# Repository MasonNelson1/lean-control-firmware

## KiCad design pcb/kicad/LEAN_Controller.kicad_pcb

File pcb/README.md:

# LEAN PCBs (Mason's KiCad project, Rev M, 2026-10-19)

Trimmed from the Drive zip on 2026-11-21: backups, gerbers, 3D exports and
fabrication zips removed. The full original is still on the team Drive.

- `kicad/` schematic (5 sheets), board, project, symbol + footprint libraries. Plain text: grep nets.
- `docs/` Mason's design notes (wiring, Bluetooth, power switch, rotary switches, panel).
- `csv/` connector pinouts, BOM, Teensy pin map (`old_number` = footprint pad, NOT Teensy pin).
- `previews/` schematic and assembly PNGs.
- `datasheets/` assembly guide, control-board V2/V3 drawings, Pololu regulator, rotary switch, VESC (TRAMPA MkVI) manual.
- `vesc-reference/` VESC hw config source and appconf parameter definitions.

## Teensy pin → net (read from the board copper, matches firmware `src/common.h`)
| Pin | Net | Pin | Net |
|---|---|---|---|
| 0 / 1 | Bluetooth TX→RX / RX←TX (Serial1, J22) | 24 / 25 / 26 | BTN LEAN / DISARM / REMOTE |
| 2 / 32 | BT EN / STATE (R65/R66 DNP, disconnected) | 27–31 | LED CAL / LEAN / DISARM / REMOTE / CONNECTED |
| 4 | Calibrate button (J5.2) | A0 / A1 | SPEED / ACCEL knob |
| 22 / 23 | CAN1 TX / RX → MCP2562 | A14–A17 | FSR4 J9 / FSR3 J8 / FSR2 J7 / FSR1 J6 |

Firmware sensor roles: J6/A17 back, J7/A16 right, J8/A15 front, J9/A14 left.
VESC: J2 primary = 5 V, GND, CANH, CANL. J1 secondary = CAN only.

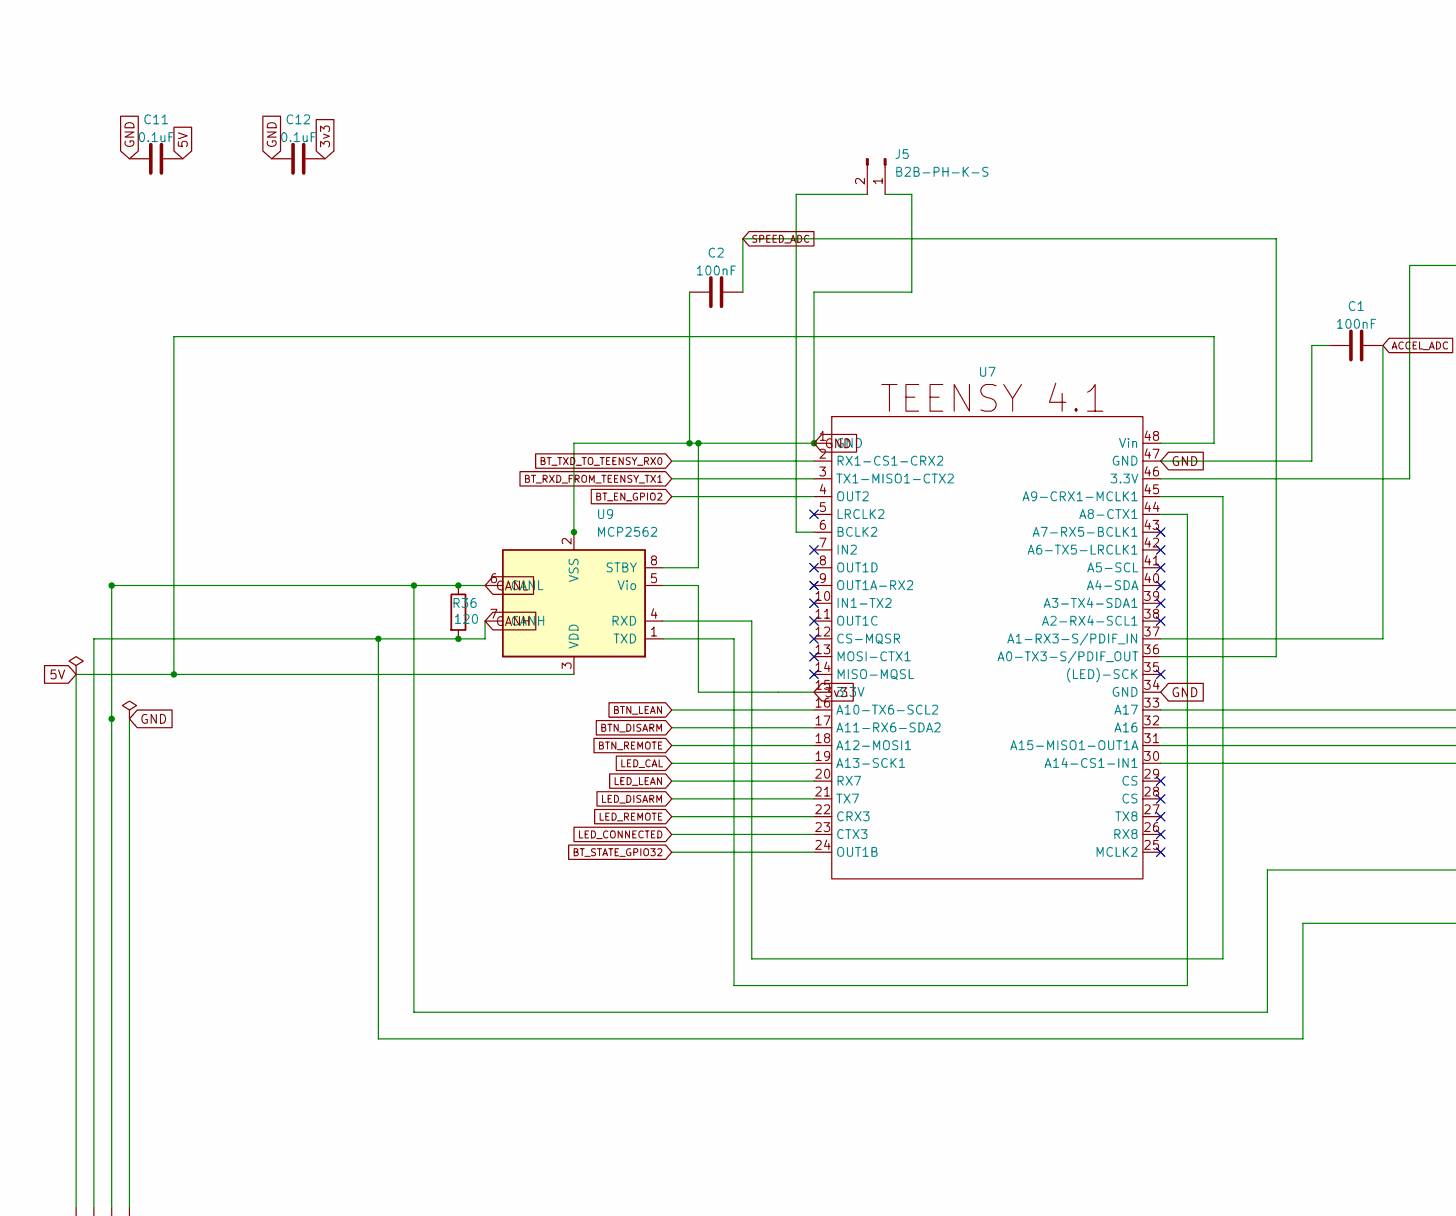
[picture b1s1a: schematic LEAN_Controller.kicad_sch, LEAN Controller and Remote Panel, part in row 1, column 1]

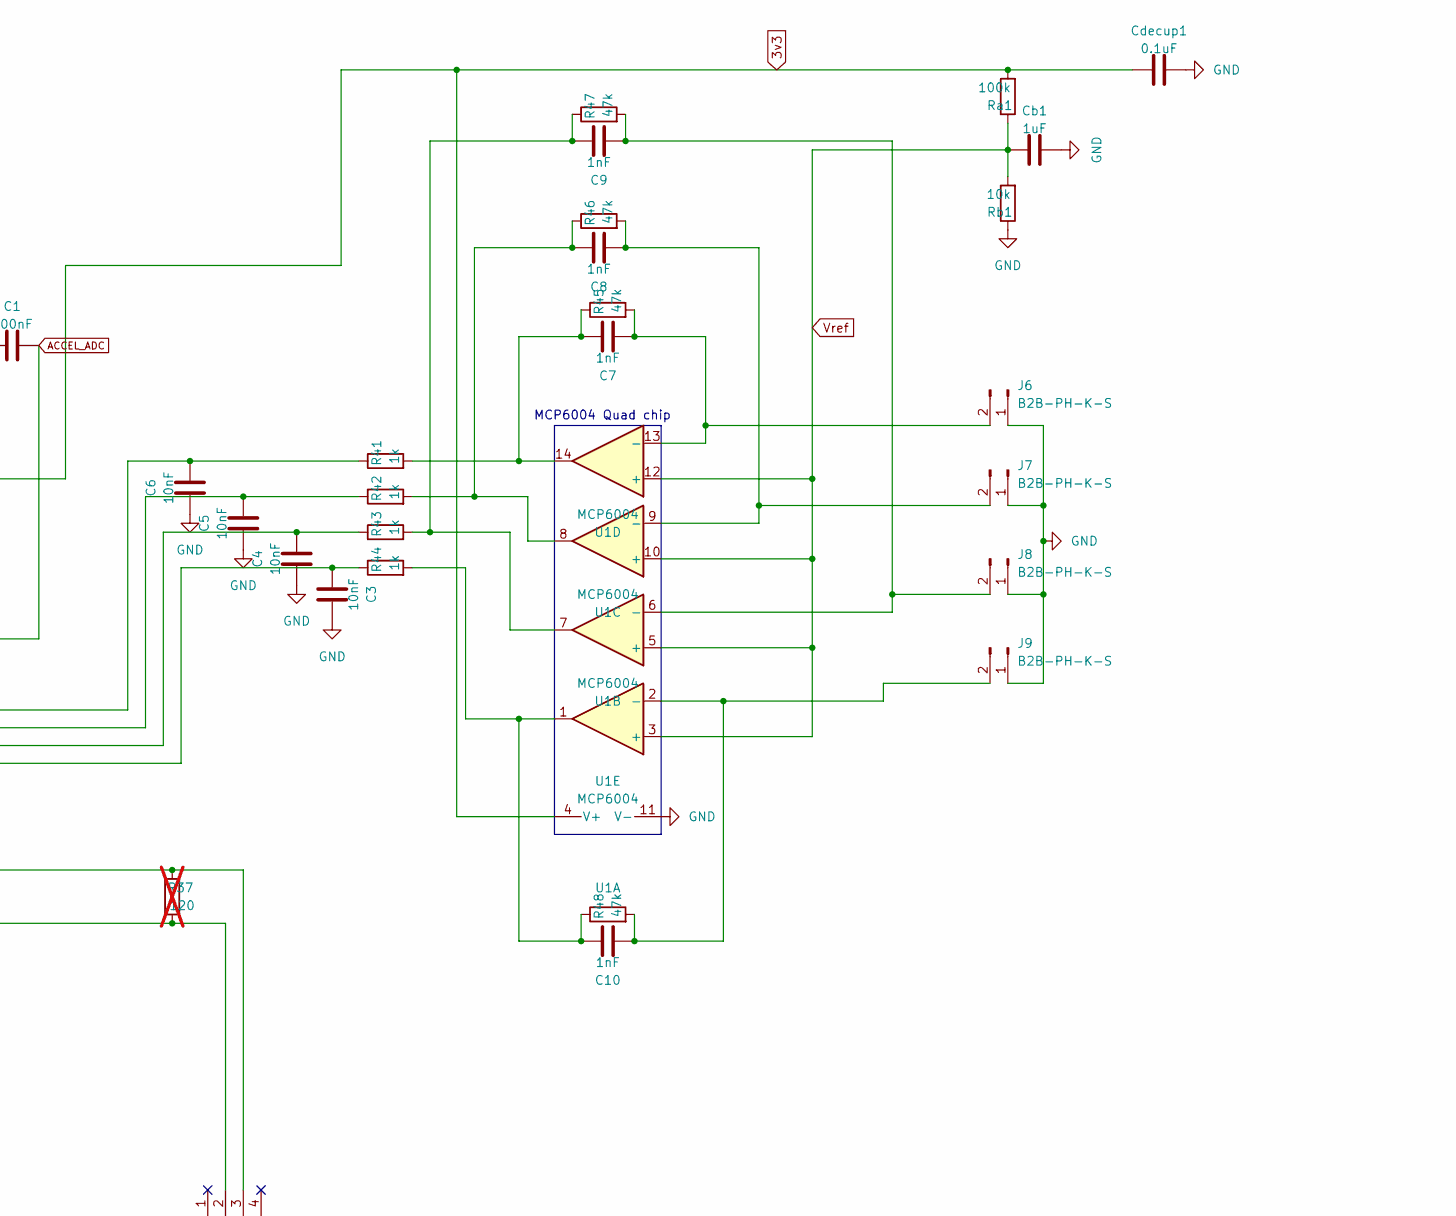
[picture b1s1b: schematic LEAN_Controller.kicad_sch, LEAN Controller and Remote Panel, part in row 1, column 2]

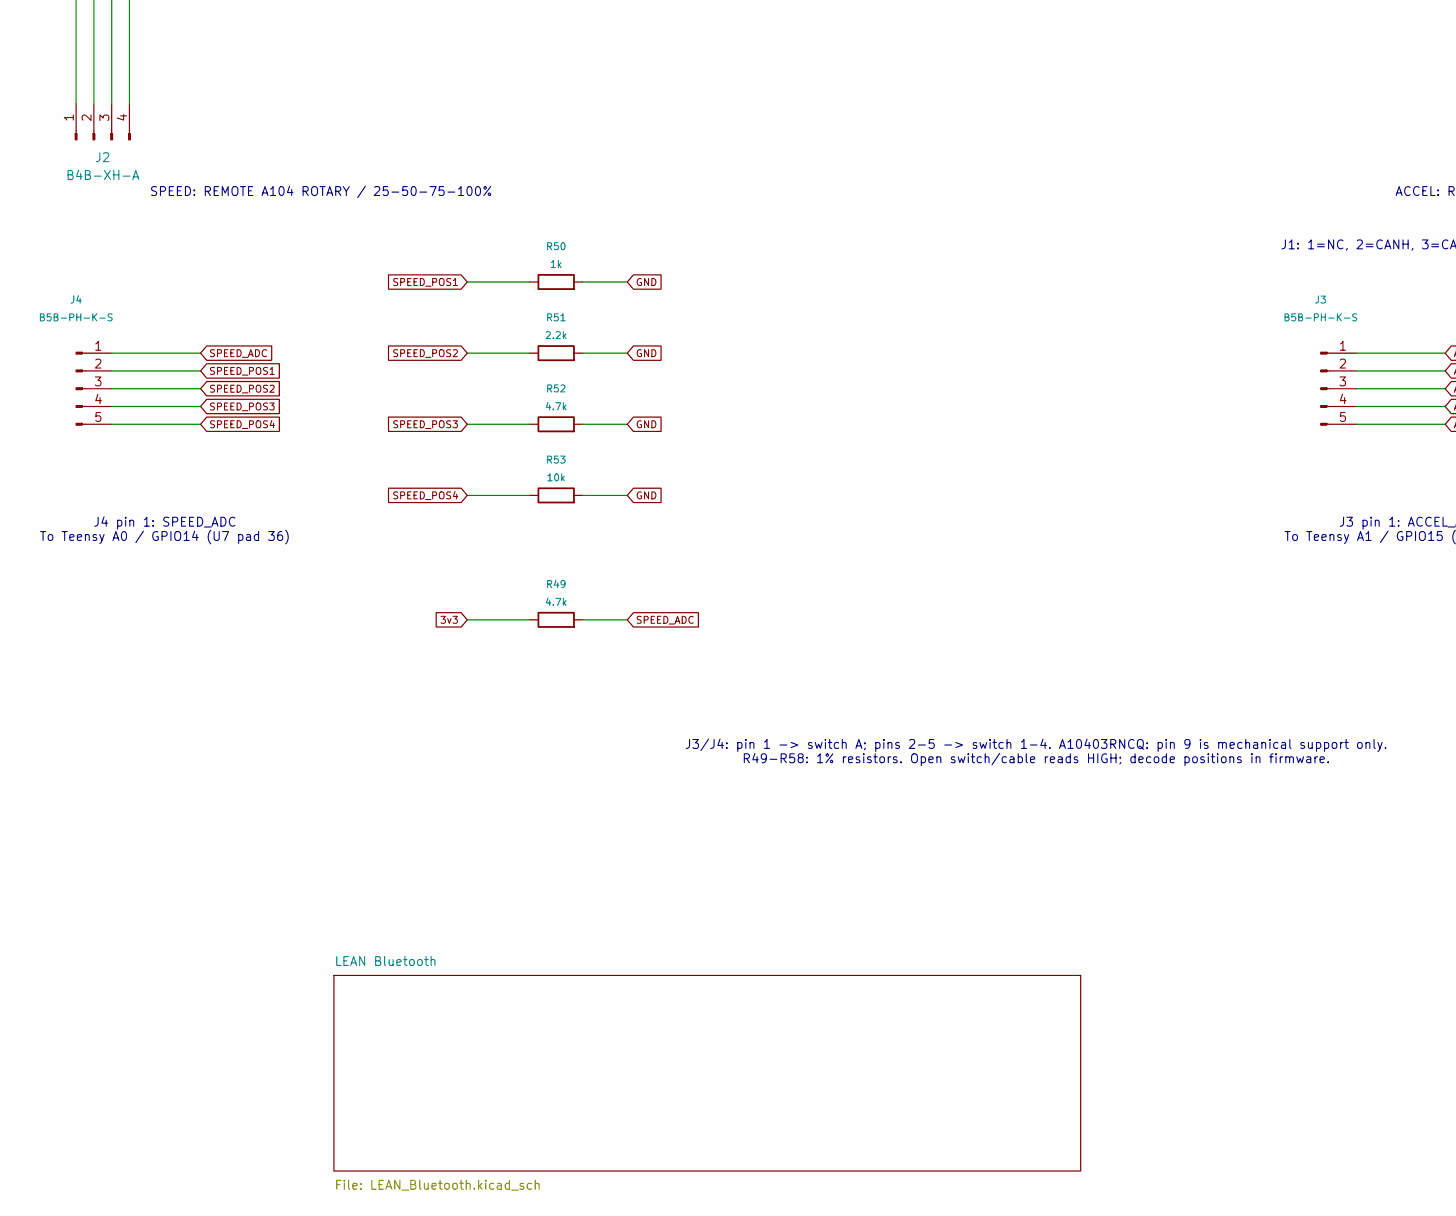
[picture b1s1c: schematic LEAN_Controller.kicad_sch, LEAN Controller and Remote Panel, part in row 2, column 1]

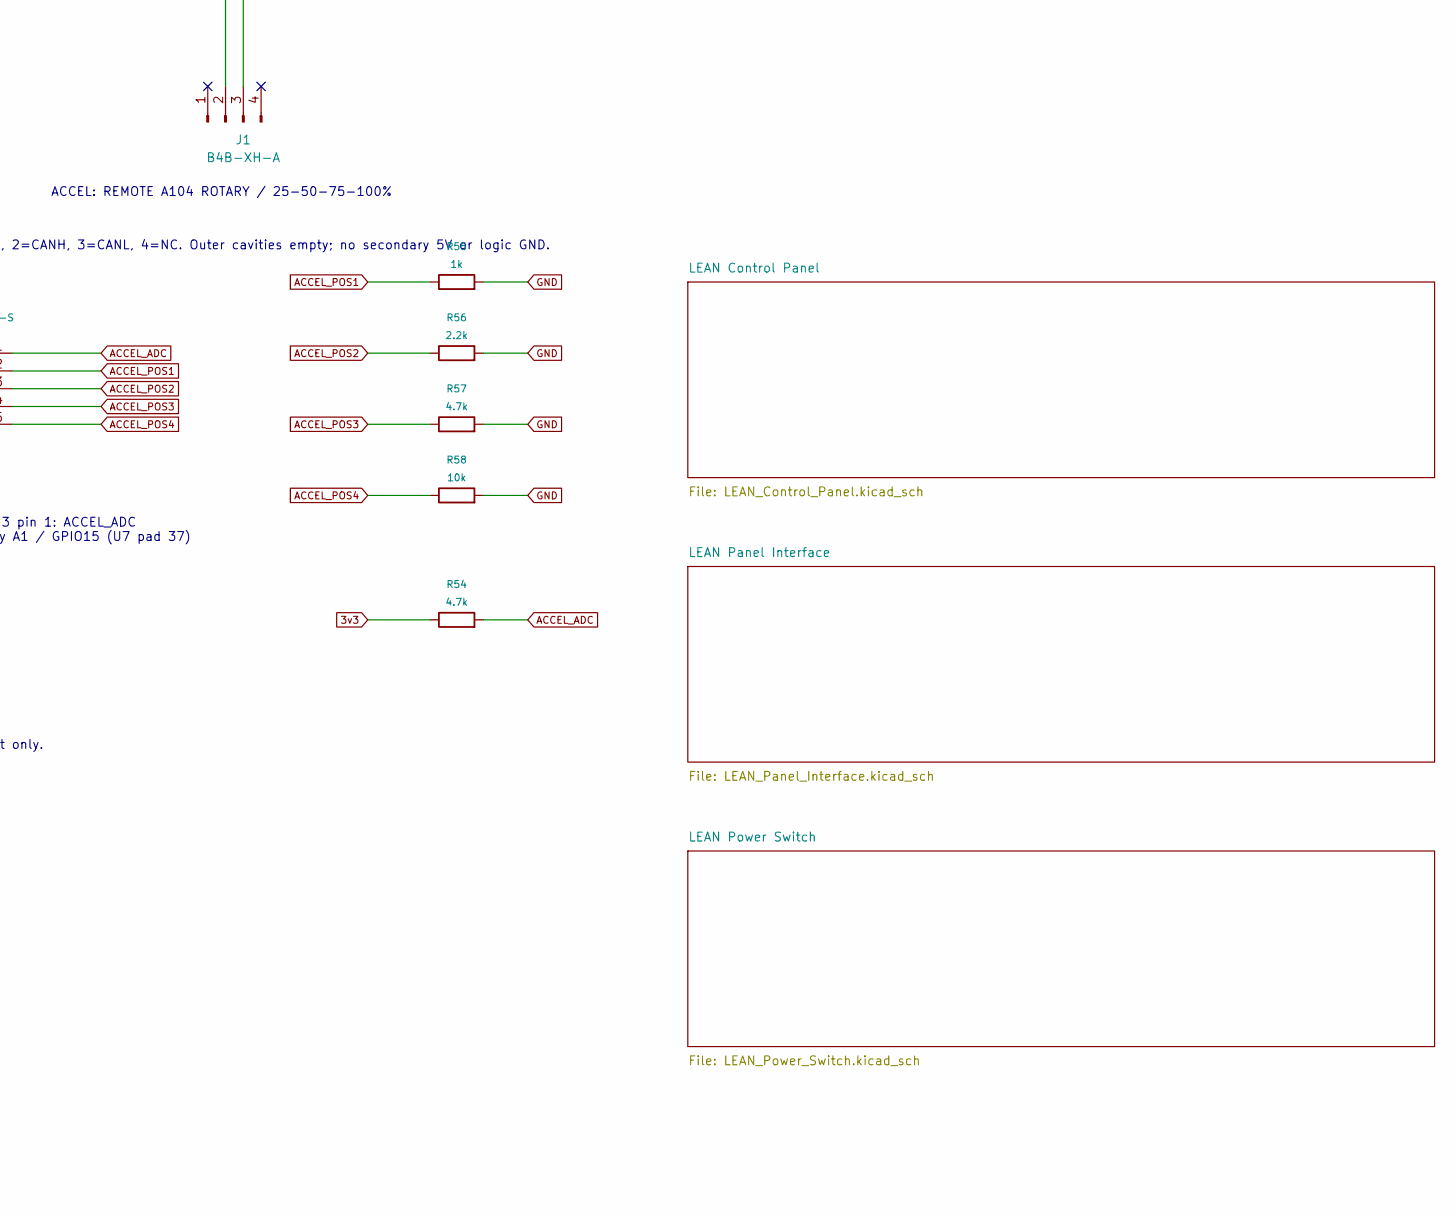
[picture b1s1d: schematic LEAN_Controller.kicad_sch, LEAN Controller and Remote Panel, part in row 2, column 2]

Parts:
C1, C2: 100nF; C_Disc_D5.0mm_W2.5mm_P5.00mm
C3, C4, C5, C6: 10nF; C_Disc_D5.0mm_W2.5mm_P5.00mm
C7, C8, C9, C10: 1nF; C_Disc_D5.0mm_W2.5mm_P5.00mm
C11, C12: 0.1uF; C_Disc_D5.0mm_W2.5mm_P5.00mm
Cb1: 1uF; C_Disc_D5.0mm_W2.5mm_P5.00mm
Cdecup1: 0.1uF; C_Disc_D5.0mm_W2.5mm_P5.00mm
J1, J2: B4B-XH-A; JST_XH_B4B-XH-A_1x04_P2.50mm_Vertical
J3, J4: B5B-PH-K-S; JST_PH_B5B-PH-K_1x05_P2.00mm_Vertical
J5, J6, J7, J8, J9: B2B-PH-K-S; JST_PH_B2B-PH-K_1x02_P2.00mm_Vertical
R36: 120; R_Axial_DIN0207_L6.3mm_D2.5mm_P7.62mm_Horizontal
R37: 120; R_Axial_DIN0207_L6.3mm_D2.5mm_P7.62mm_Horizontal; not fitted
R41, R42, R43, R44, R50, R55: 1k; R_Axial_DIN0207_L6.3mm_D2.5mm_P7.62mm_Horizontal
R45, R46, R47, R48: 47k; R_Axial_DIN0207_L6.3mm_D2.5mm_P7.62mm_Horizontal
R49, R52, R54, R57: 4.7k; R_Axial_DIN0207_L6.3mm_D2.5mm_P7.62mm_Horizontal
R51, R56: 2.2k; R_Axial_DIN0207_L6.3mm_D2.5mm_P7.62mm_Horizontal
R53, R58: 10k; R_Axial_DIN0207_L6.3mm_D2.5mm_P7.62mm_Horizontal
Ra1: 100k; R_Axial_DIN0207_L6.3mm_D2.5mm_P7.62mm_Horizontal
Rb1: 10k; R_Axial_DIN0207_L6.3mm_D2.5mm_P7.62mm_Horizontal
U1: MCP6004; DIP-14_W7.62mm
U7: Teensy41
U9: MCP2562; DIP-8_W7.62mm

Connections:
3v3: C12.2, Cdecup1.1, R49.1, R54.1, Ra1.2, U1.4 (V+), U7.15 (A1-RX3-S/PDIF_IN), U7.46 (3.3V), U9.5 (Vio); also elsewhere on the board
5V: C11.2, J2.1, U7.48 (Vin), U9.3 (VDD); also elsewhere on the board
ACCEL_ADC: C1.2, J3.1, R54.2, U7.37 (CS)
ACCEL_POS1: J3.2, R55.1
ACCEL_POS2: J3.3, R56.1
ACCEL_POS3: J3.4, R57.1
ACCEL_POS4: J3.5, R58.1
BTN_DISARM: U7.17 (A3-TX4-SDA1); also elsewhere on the board
BTN_LEAN: U7.16 (A2-RX4-SCL1); also elsewhere on the board
BTN_REMOTE: U7.18 (A4-SDA); also elsewhere on the board
BT_EN_GPIO2: U7.4 (BCLK2); also elsewhere on the board
BT_RXD_FROM_TEENSY_TX1: U7.3 (LRCLK2); also elsewhere on the board
BT_STATE_GPIO32: U7.24 (A10-TX6-SCL2); also elsewhere on the board
BT_TXD_TO_TEENSY_RX0: U7.2 (OUT2); also elsewhere on the board
CANH: J1.2, J2.2, R36.2, R37.2, U9.7 (CANH)
CANL: J1.3, J2.3, R36.1, R37.1, U9.6 (CANL)
GND: C1.1, C2.1, C3.2, C4.1, C5.1, C6.1, C11.1, C12.1, Cb1.2, Cdecup1.2, J2.4, J5.1, J6.1, J7.1, J8.1, J9.1, R50.2, R51.2, R52.2, R53.2, R55.2, R56.2, R57.2, R58.2, Rb1.1, U1.11 (V-), U7.1 (TX1-MISO1-CTX2), U7.34 (RX8), U7.47 (GND), U9.2 (VSS), U9.8 (STBY); also elsewhere on the board
LED_CAL: U7.19 (A5-SCL); also elsewhere on the board
LED_CONNECTED: U7.23 (A9-CRX1-MCLK1); also elsewhere on the board
LED_DISARM: U7.21 (A7-RX5-BCLK1); also elsewhere on the board
LED_LEAN: U7.20 (A6-TX5-LRCLK1); also elsewhere on the board
LED_REMOTE: U7.22 (A8-CTX1); also elsewhere on the board
unnamed: C7.2, R41.2, R45.1, U1.14
unnamed: C8.2, R42.2, R46.1, U1.8
unnamed: C9.2, R43.2, R47.1, U1.7
unnamed: C10.2, R44.2, R48.1, U1.1
unnamed: J5.2, U7.6 (OUT1D)
unnamed: C7.1, J6.2, R45.2, U1.13 (-)
unnamed: C8.1, J7.2, R46.2, U1.9 (-)
unnamed: C9.1, J8.2, R47.2, U1.6 (-)
unnamed: C10.1, J9.2, R48.2, U1.2 (-)
unnamed: U7.44 (A8-CTX1), U9.1 (TXD)
unnamed: U7.45 (A9-CRX1-MCLK1), U9.4 (RXD)
unnamed: C3.1, R44.1, U7.30 (CRX3)
unnamed: C4.2, R43.1, U7.31 (CTX3)
unnamed: C5.2, R42.1, U7.32 (OUT1B)
unnamed: C6.2, R41.1, U7.33 (MCLK2)
SPEED_ADC: C2.2, J4.1, R49.2, U7.36 (CS)
SPEED_POS1: J4.2, R50.1
SPEED_POS2: J4.3, R51.1
SPEED_POS3: J4.4, R52.1
SPEED_POS4: J4.5, R53.1
Vref: Cb1.1, Ra1.1, Rb1.2, U1.3 (+), U1.5 (+), U1.10 (+), U1.12 (+)

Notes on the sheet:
MCP6004 Quad chip
SPEED: REMOTE A104 ROTARY / 25-50-75-100%
ACCEL: REMOTE A104 ROTARY / 25-50-75-100%
J3/J4: pin 1 -> switch A; pins 2-5 -> switch 1-4. A10403RNCQ: pin 9 is mechanical support only. R49-R58: 1% resistors. Open switch/cable reads HIGH; decode positions in firmware.
J4 pin 1: SPEED_ADC To Teensy A0 / GPIO14 (U7 pad 36)
J3 pin 1: ACCEL_ADC To Teensy A1 / GPIO15 (U7 pad 37)
J1: 1=NC, 2=CANH, 3=CANL, 4=NC. Outer cavities empty; no secondary 5V or logic GND.

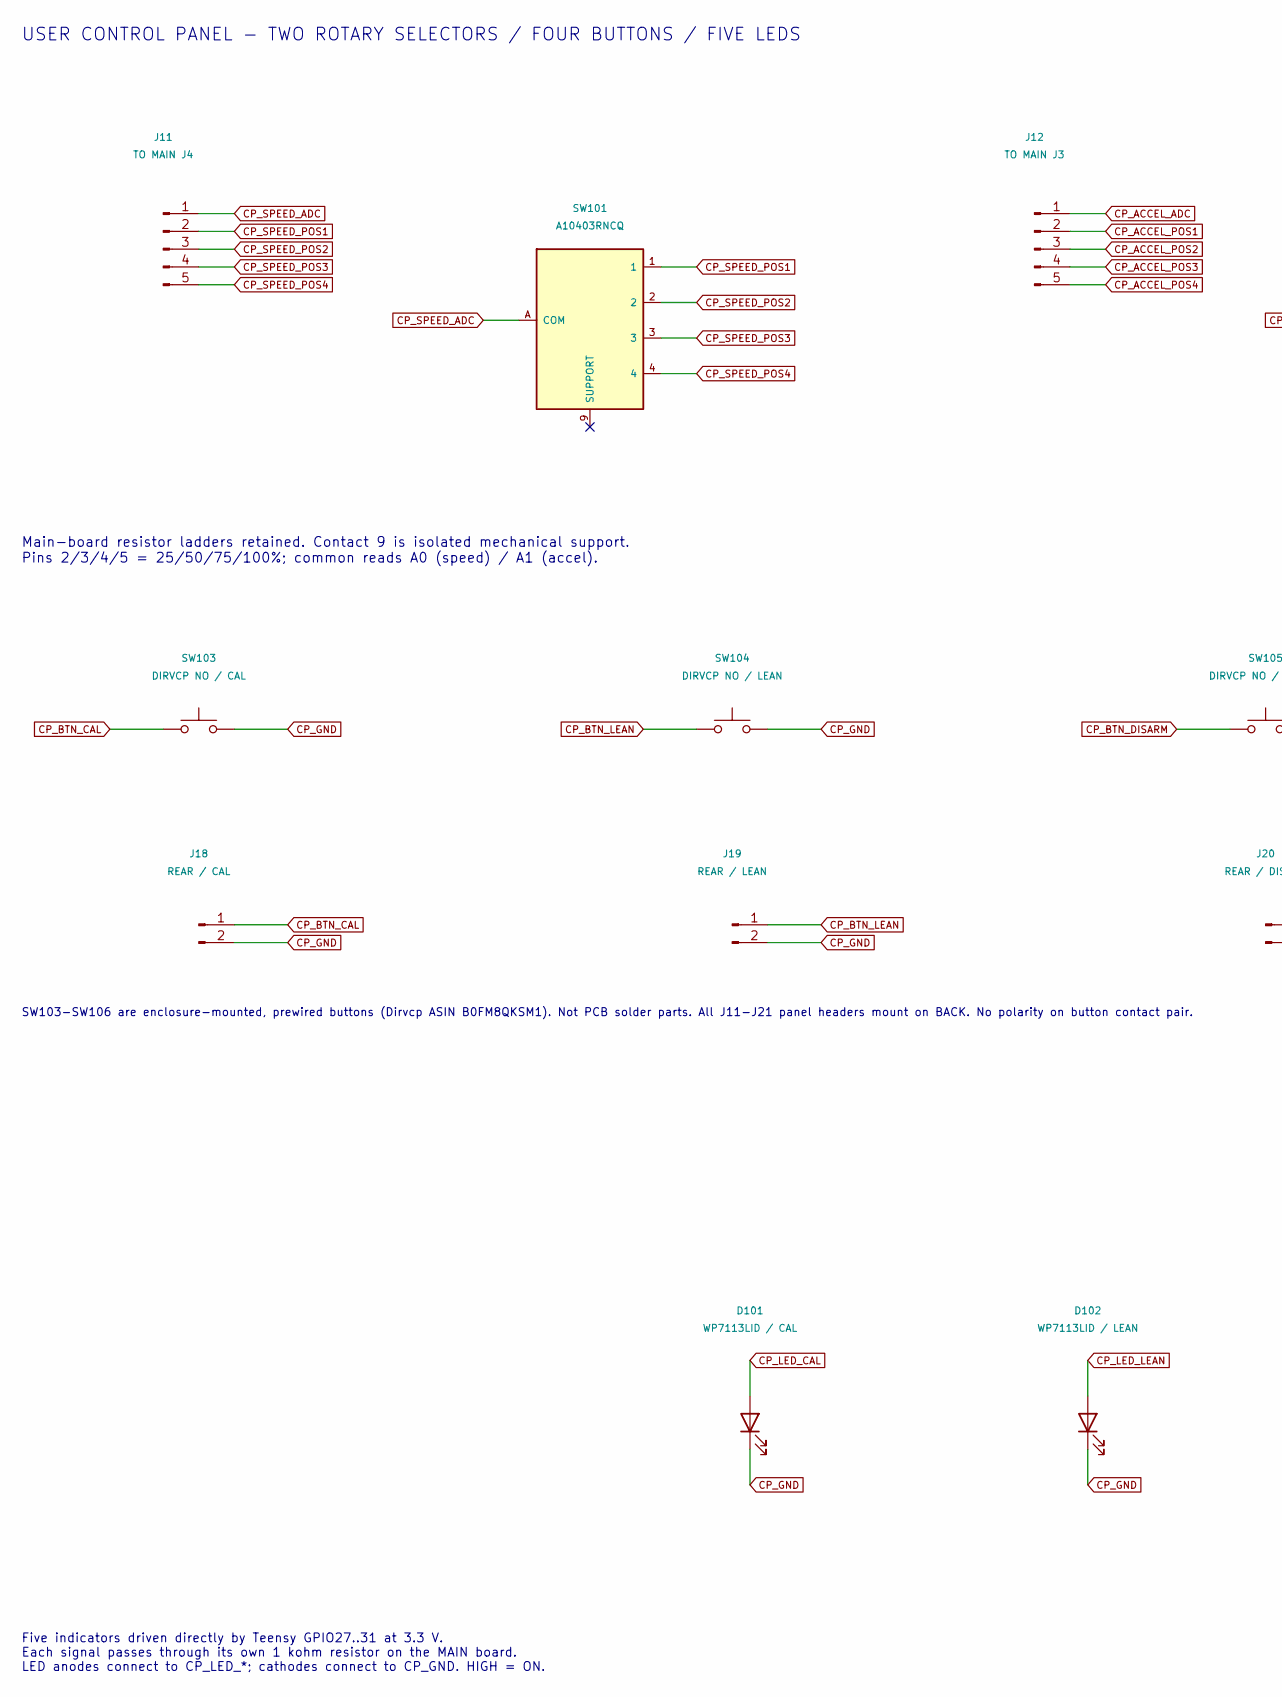
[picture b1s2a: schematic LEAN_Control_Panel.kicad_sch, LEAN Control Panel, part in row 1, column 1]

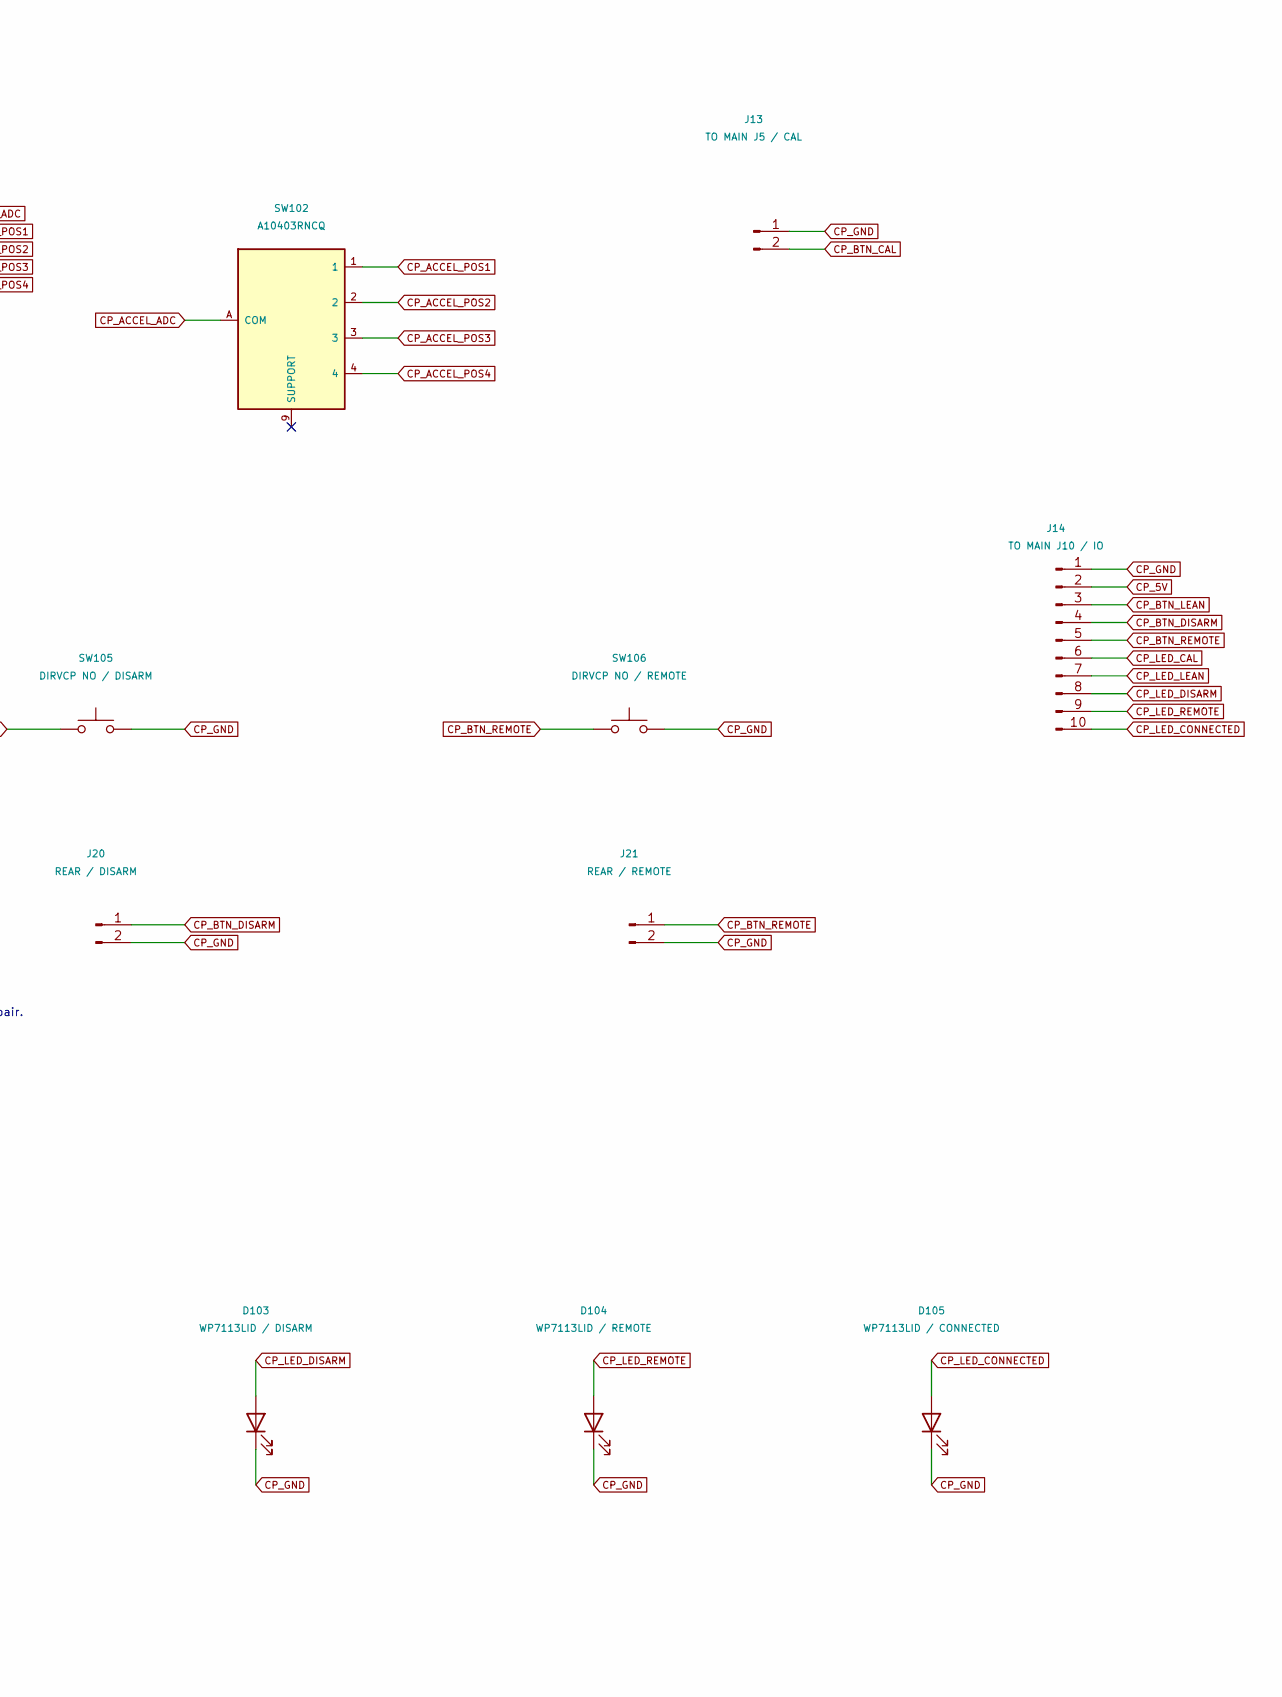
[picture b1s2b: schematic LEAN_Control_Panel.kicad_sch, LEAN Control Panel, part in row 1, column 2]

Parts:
D101: WP7113LID / CAL; LED_D5.0mm
D102: WP7113LID / LEAN; LED_D5.0mm
D103: WP7113LID / DISARM; LED_D5.0mm
D104: WP7113LID / REMOTE; LED_D5.0mm
D105: WP7113LID / CONNECTED; LED_D5.0mm
J11: TO MAIN J4; JST_PH_B5B-PH-K_1x05_P2.00mm_Vertical
J12: TO MAIN J3; JST_PH_B5B-PH-K_1x05_P2.00mm_Vertical
J13: TO MAIN J5 / CAL; JST_PH_B2B-PH-K_1x02_P2.00mm_Vertical
J14: TO MAIN J10 / IO; JST_PH_B10B-PH-K_1x10_P2.00mm_Vertical
J18: REAR / CAL; JST_PH_B2B-PH-K_1x02_P2.00mm_Vertical
J19: REAR / LEAN; JST_PH_B2B-PH-K_1x02_P2.00mm_Vertical
J20: REAR / DISARM; JST_PH_B2B-PH-K_1x02_P2.00mm_Vertical
J21: REAR / REMOTE; JST_PH_B2B-PH-K_1x02_P2.00mm_Vertical
SW101, SW102: A10403RNCQ; SW_Rotary_CK_A10403RNCQ
SW103: DIRVCP NO / CAL
SW104: DIRVCP NO / LEAN
SW105: DIRVCP NO / DISARM
SW106: DIRVCP NO / REMOTE

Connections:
CP_5V: J14.2; also elsewhere on the board
CP_ACCEL_ADC: J12.1, SW102.A (COM)
CP_ACCEL_POS1: J12.2, SW102.1
CP_ACCEL_POS2: J12.3, SW102.2
CP_ACCEL_POS3: J12.4, SW102.3
CP_ACCEL_POS4: J12.5, SW102.4
CP_BTN_CAL: J13.2, J18.1, SW103.1
CP_BTN_DISARM: J14.4, J20.1, SW105.1
CP_BTN_LEAN: J14.3, J19.1, SW104.1
CP_BTN_REMOTE: J14.5, J21.1, SW106.1
CP_GND: D101.1 (K), D102.1 (K), D103.1 (K), D104.1 (K), D105.1 (K), J13.1, J14.1, J18.2, J19.2, J20.2, J21.2, SW103.2, SW104.2, SW105.2, SW106.2; also elsewhere on the board
CP_LED_CAL: D101.2 (A), J14.6
CP_LED_CONNECTED: D105.2 (A), J14.10
CP_LED_DISARM: D103.2 (A), J14.8
CP_LED_LEAN: D102.2 (A), J14.7
CP_LED_REMOTE: D104.2 (A), J14.9
CP_SPEED_ADC: J11.1, SW101.A (COM)
CP_SPEED_POS1: J11.2, SW101.1
CP_SPEED_POS2: J11.3, SW101.2
CP_SPEED_POS3: J11.4, SW101.3
CP_SPEED_POS4: J11.5, SW101.4

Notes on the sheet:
USER CONTROL PANEL - TWO ROTARY SELECTORS / FOUR BUTTONS / FIVE LEDS
Main-board resistor ladders retained. Contact 9 is isolated mechanical support. Pins 2/3/4/5 = 25/50/75/100%; common reads A0 (speed) / A1 (accel).
Five indicators driven directly by Teensy GPIO27..31 at 3.3 V. Each signal passes through its own 1 kohm resistor on the MAIN board. LED anodes connect to CP_LED_*; cathodes connect to CP_GND. HIGH = ON.
SW103-SW106 are enclosure-mounted, prewired buttons (Dirvcp ASIN B0FM8QKSM1). Not PCB solder parts. All J11-J21 panel headers mount on BACK. No polarity on button contact pair.

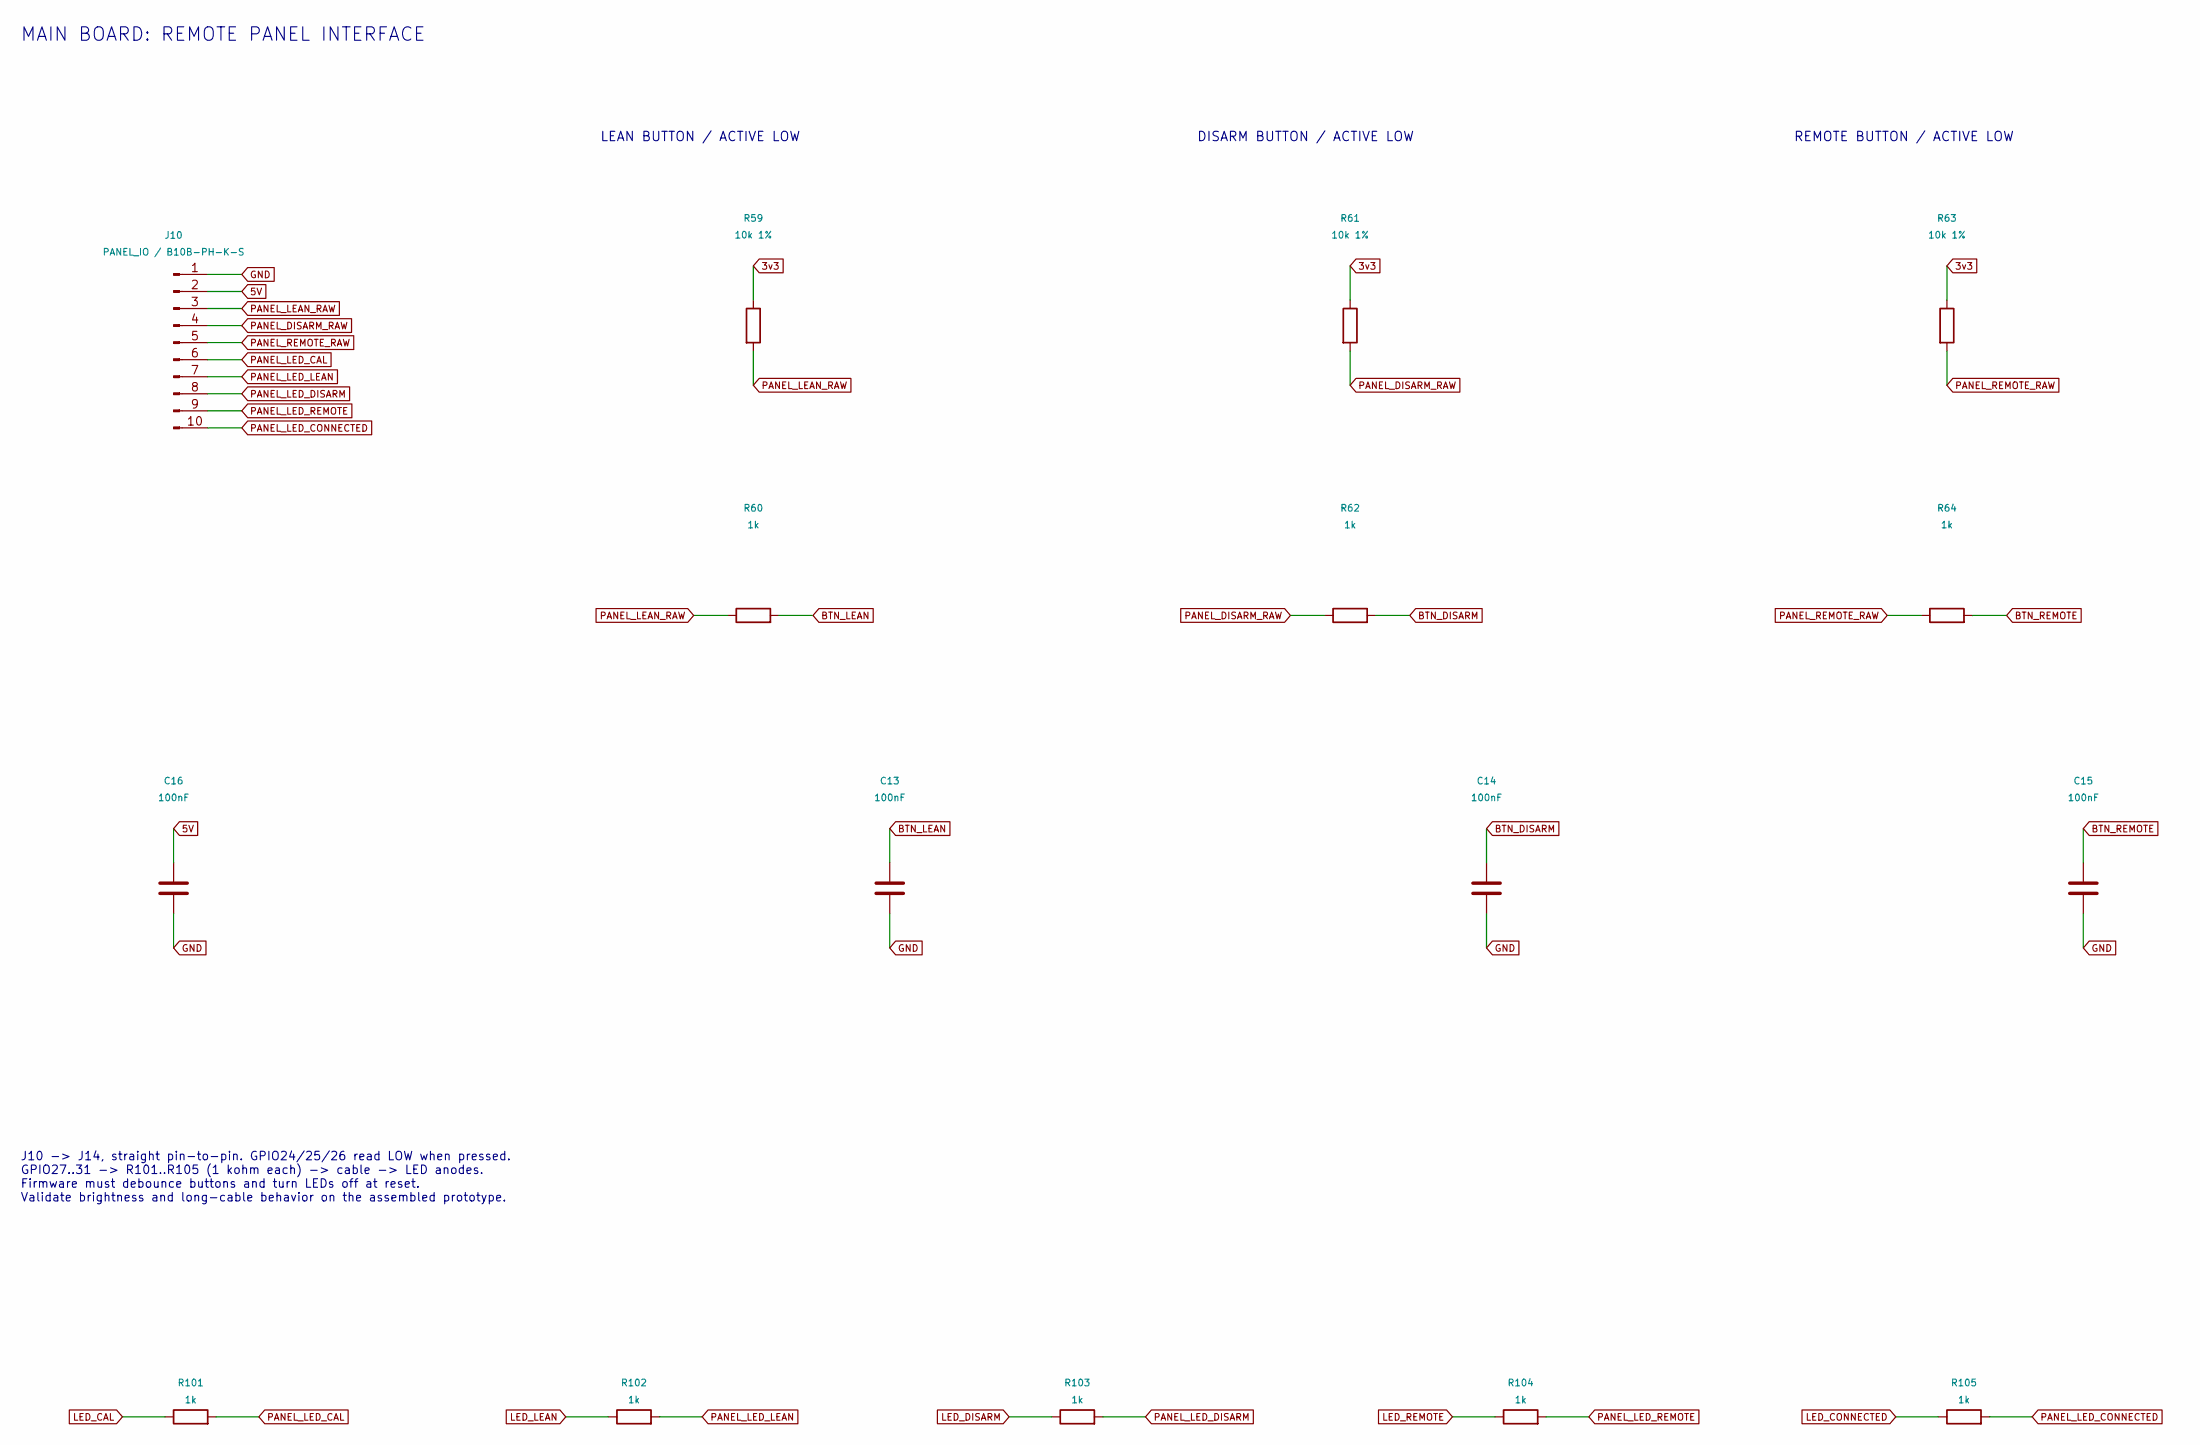
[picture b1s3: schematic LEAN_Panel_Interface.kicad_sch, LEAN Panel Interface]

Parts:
C13, C14, C15, C16: 100nF; C_Disc_D5.0mm_W2.5mm_P5.00mm
J10: PANEL_IO / B10B-PH-K-S; JST_PH_B10B-PH-K_1x10_P2.00mm_Vertical
R59, R61, R63: 10k 1%; R_Axial_DIN0207_L6.3mm_D2.5mm_P7.62mm_Horizontal
R60, R62, R64, R101, R102, R103, R104, R105: 1k; R_Axial_DIN0207_L6.3mm_D2.5mm_P7.62mm_Horizontal

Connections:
3v3: R59.1, R61.1, R63.1; also elsewhere on the board
5V: C16.1, J10.2; also elsewhere on the board
BTN_DISARM: C14.1, R62.2; also elsewhere on the board
BTN_LEAN: C13.1, R60.2; also elsewhere on the board
BTN_REMOTE: C15.1, R64.2; also elsewhere on the board
GND: C13.2, C14.2, C15.2, C16.2, J10.1; also elsewhere on the board
LED_CAL: R101.1; also elsewhere on the board
LED_CONNECTED: R105.1; also elsewhere on the board
LED_DISARM: R103.1; also elsewhere on the board
LED_LEAN: R102.1; also elsewhere on the board
LED_REMOTE: R104.1; also elsewhere on the board
PANEL_DISARM_RAW: J10.4, R61.2, R62.1
PANEL_LEAN_RAW: J10.3, R59.2, R60.1
PANEL_LED_CAL: J10.6, R101.2
PANEL_LED_CONNECTED: J10.10, R105.2
PANEL_LED_DISARM: J10.8, R103.2
PANEL_LED_LEAN: J10.7, R102.2
PANEL_LED_REMOTE: J10.9, R104.2
PANEL_REMOTE_RAW: J10.5, R63.2, R64.1

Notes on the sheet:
MAIN BOARD: REMOTE PANEL INTERFACE
LEAN BUTTON / ACTIVE LOW
DISARM BUTTON / ACTIVE LOW
REMOTE BUTTON / ACTIVE LOW
J10 -> J14, straight pin-to-pin. GPIO24/25/26 read LOW when pressed. GPIO27..31 -> R101..R105 (1 kohm each) -> cable -> LED anodes. Firmware must debounce buttons and turn LEDs off at reset. Validate brightness and long-cable behavior on the assembled prototype.
